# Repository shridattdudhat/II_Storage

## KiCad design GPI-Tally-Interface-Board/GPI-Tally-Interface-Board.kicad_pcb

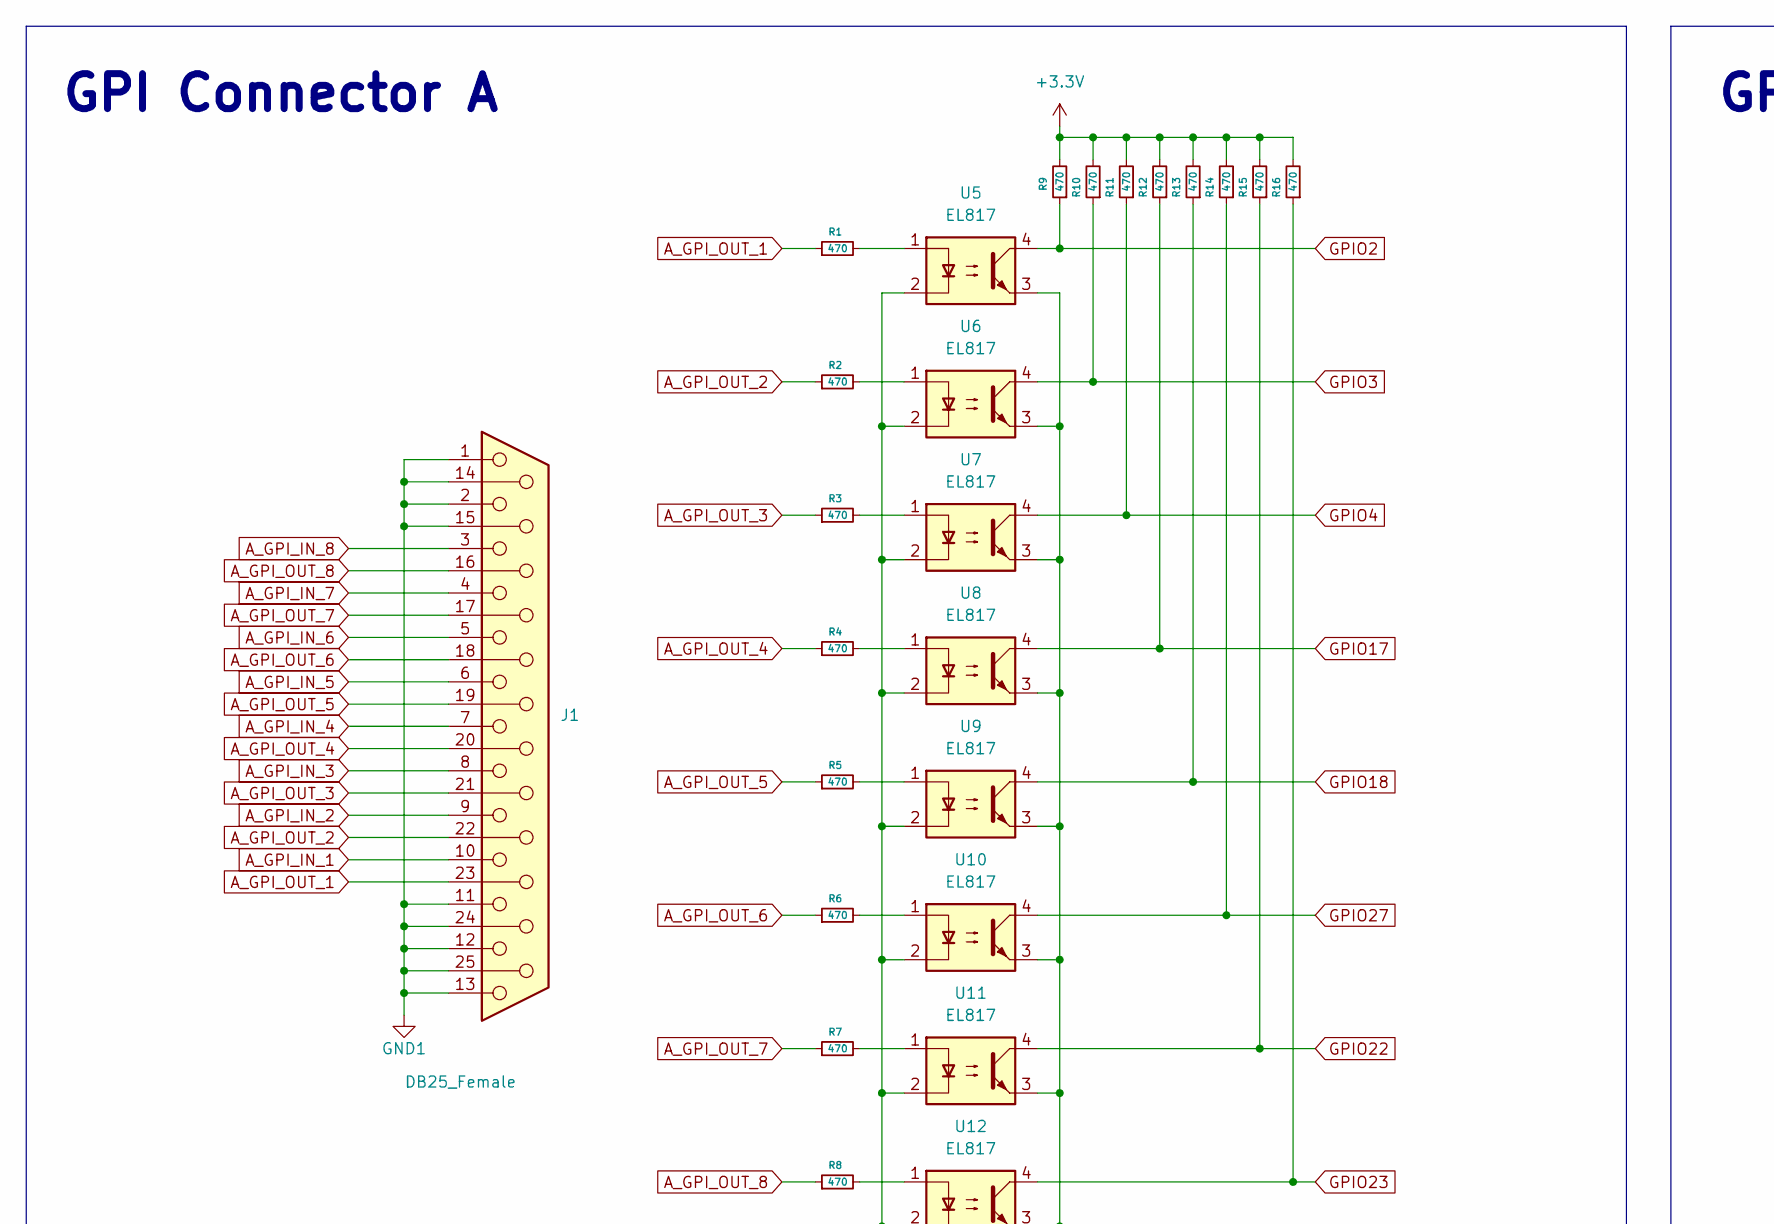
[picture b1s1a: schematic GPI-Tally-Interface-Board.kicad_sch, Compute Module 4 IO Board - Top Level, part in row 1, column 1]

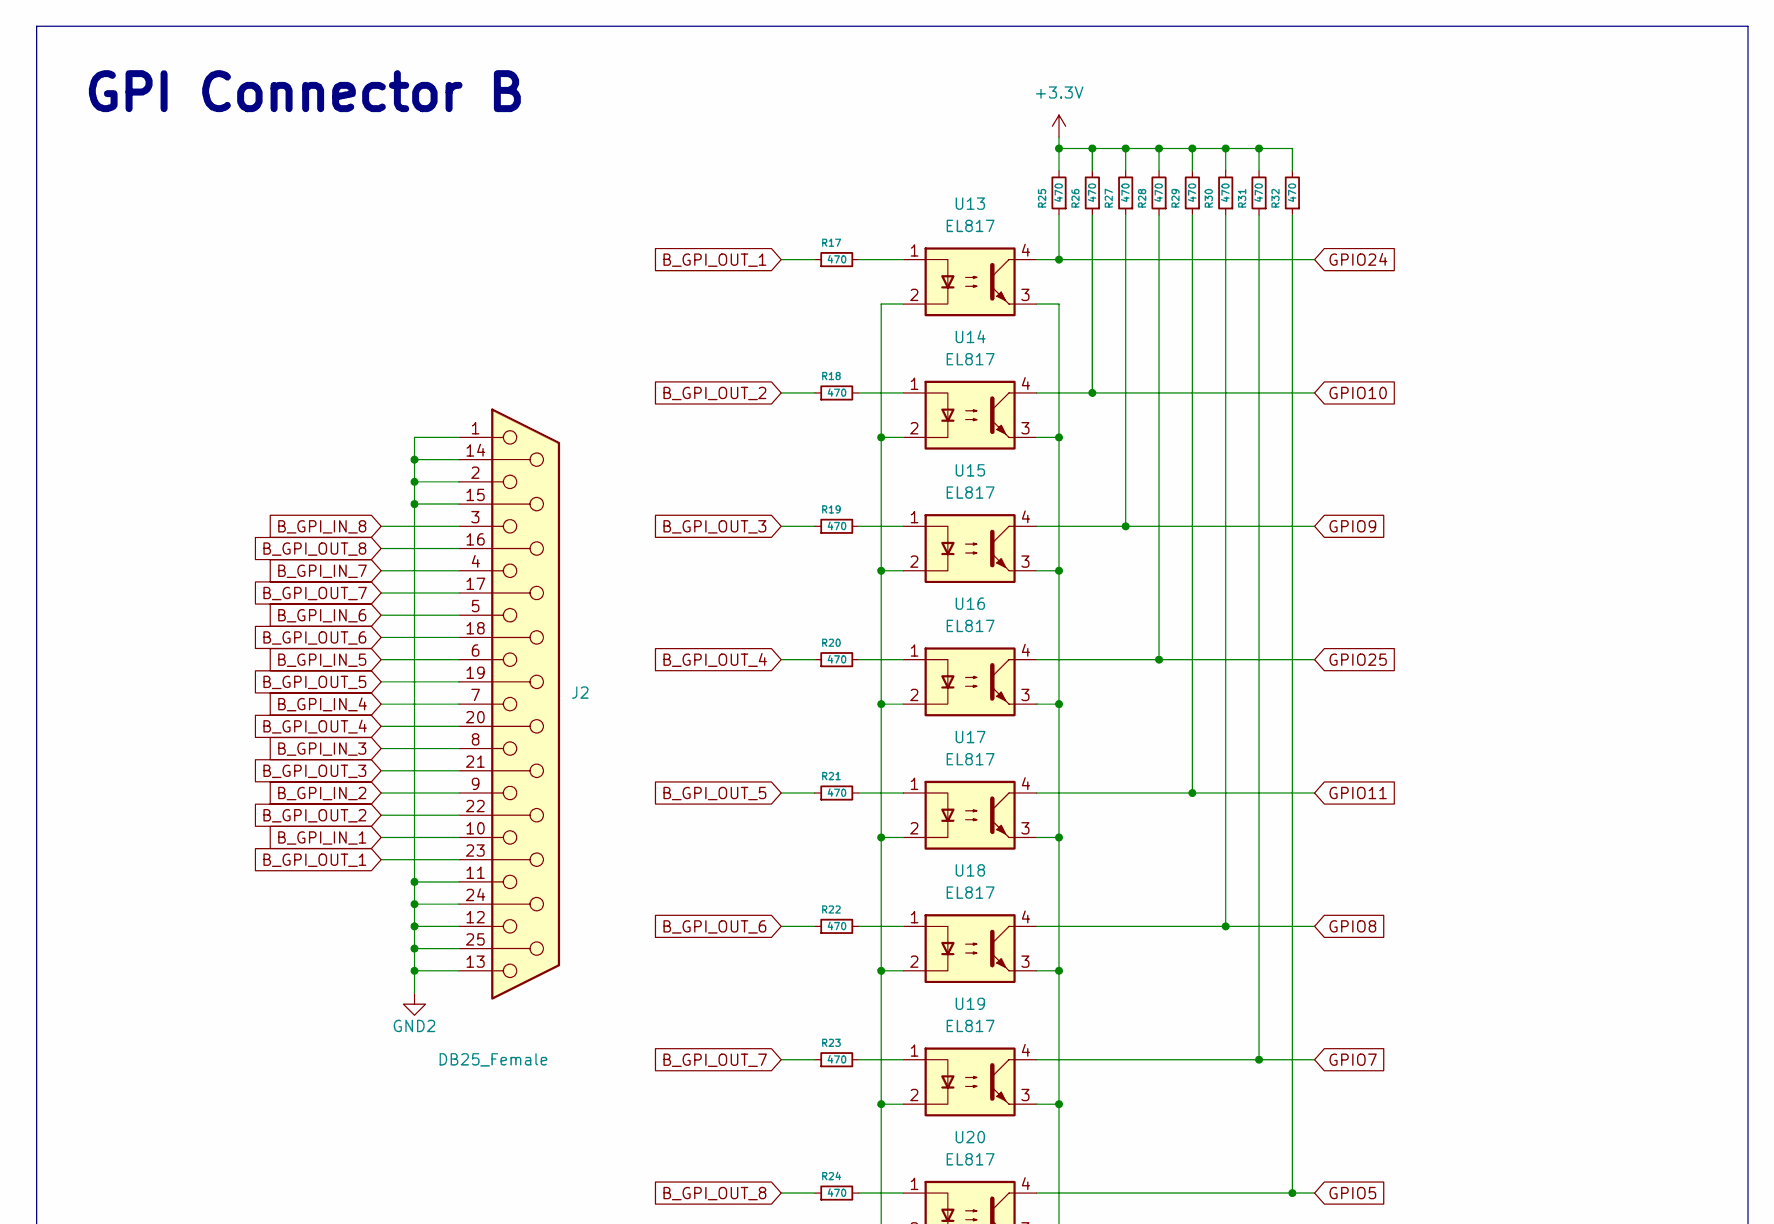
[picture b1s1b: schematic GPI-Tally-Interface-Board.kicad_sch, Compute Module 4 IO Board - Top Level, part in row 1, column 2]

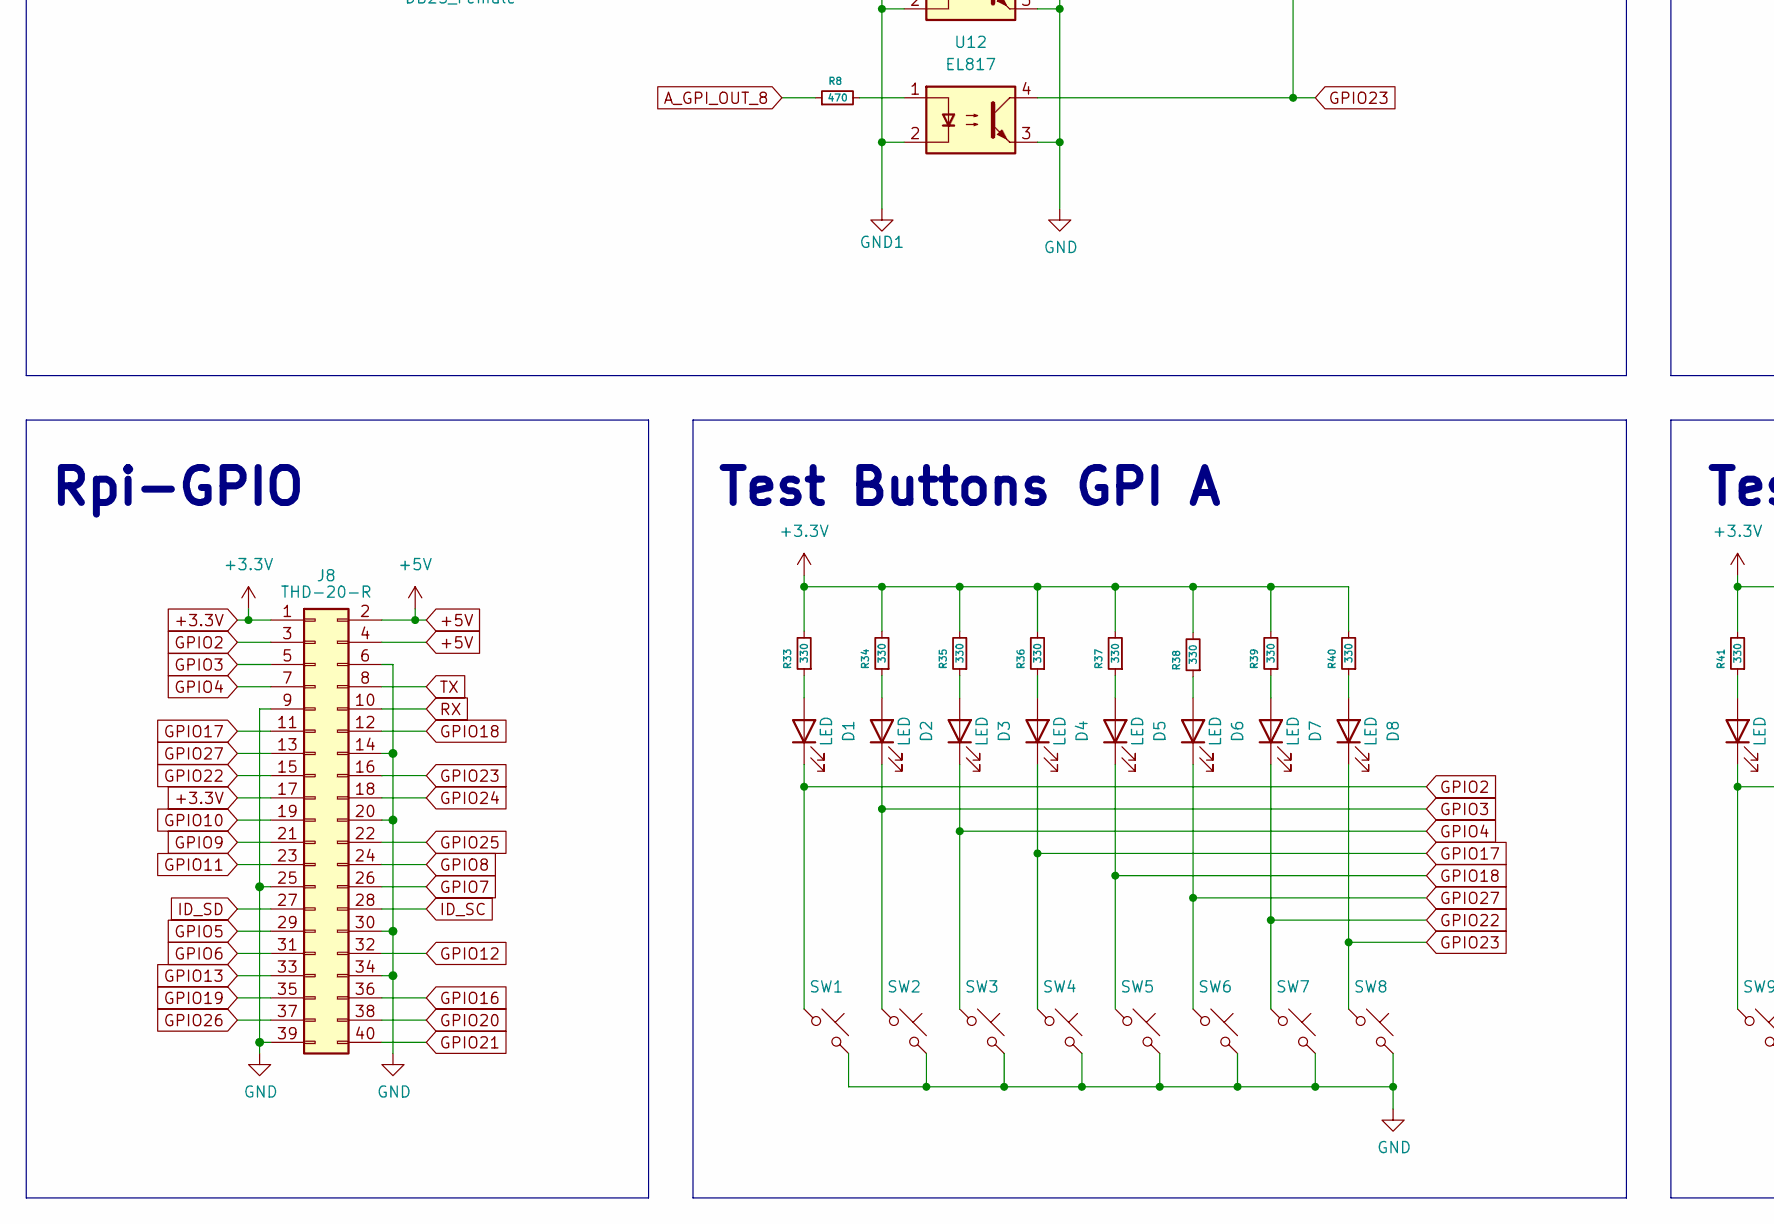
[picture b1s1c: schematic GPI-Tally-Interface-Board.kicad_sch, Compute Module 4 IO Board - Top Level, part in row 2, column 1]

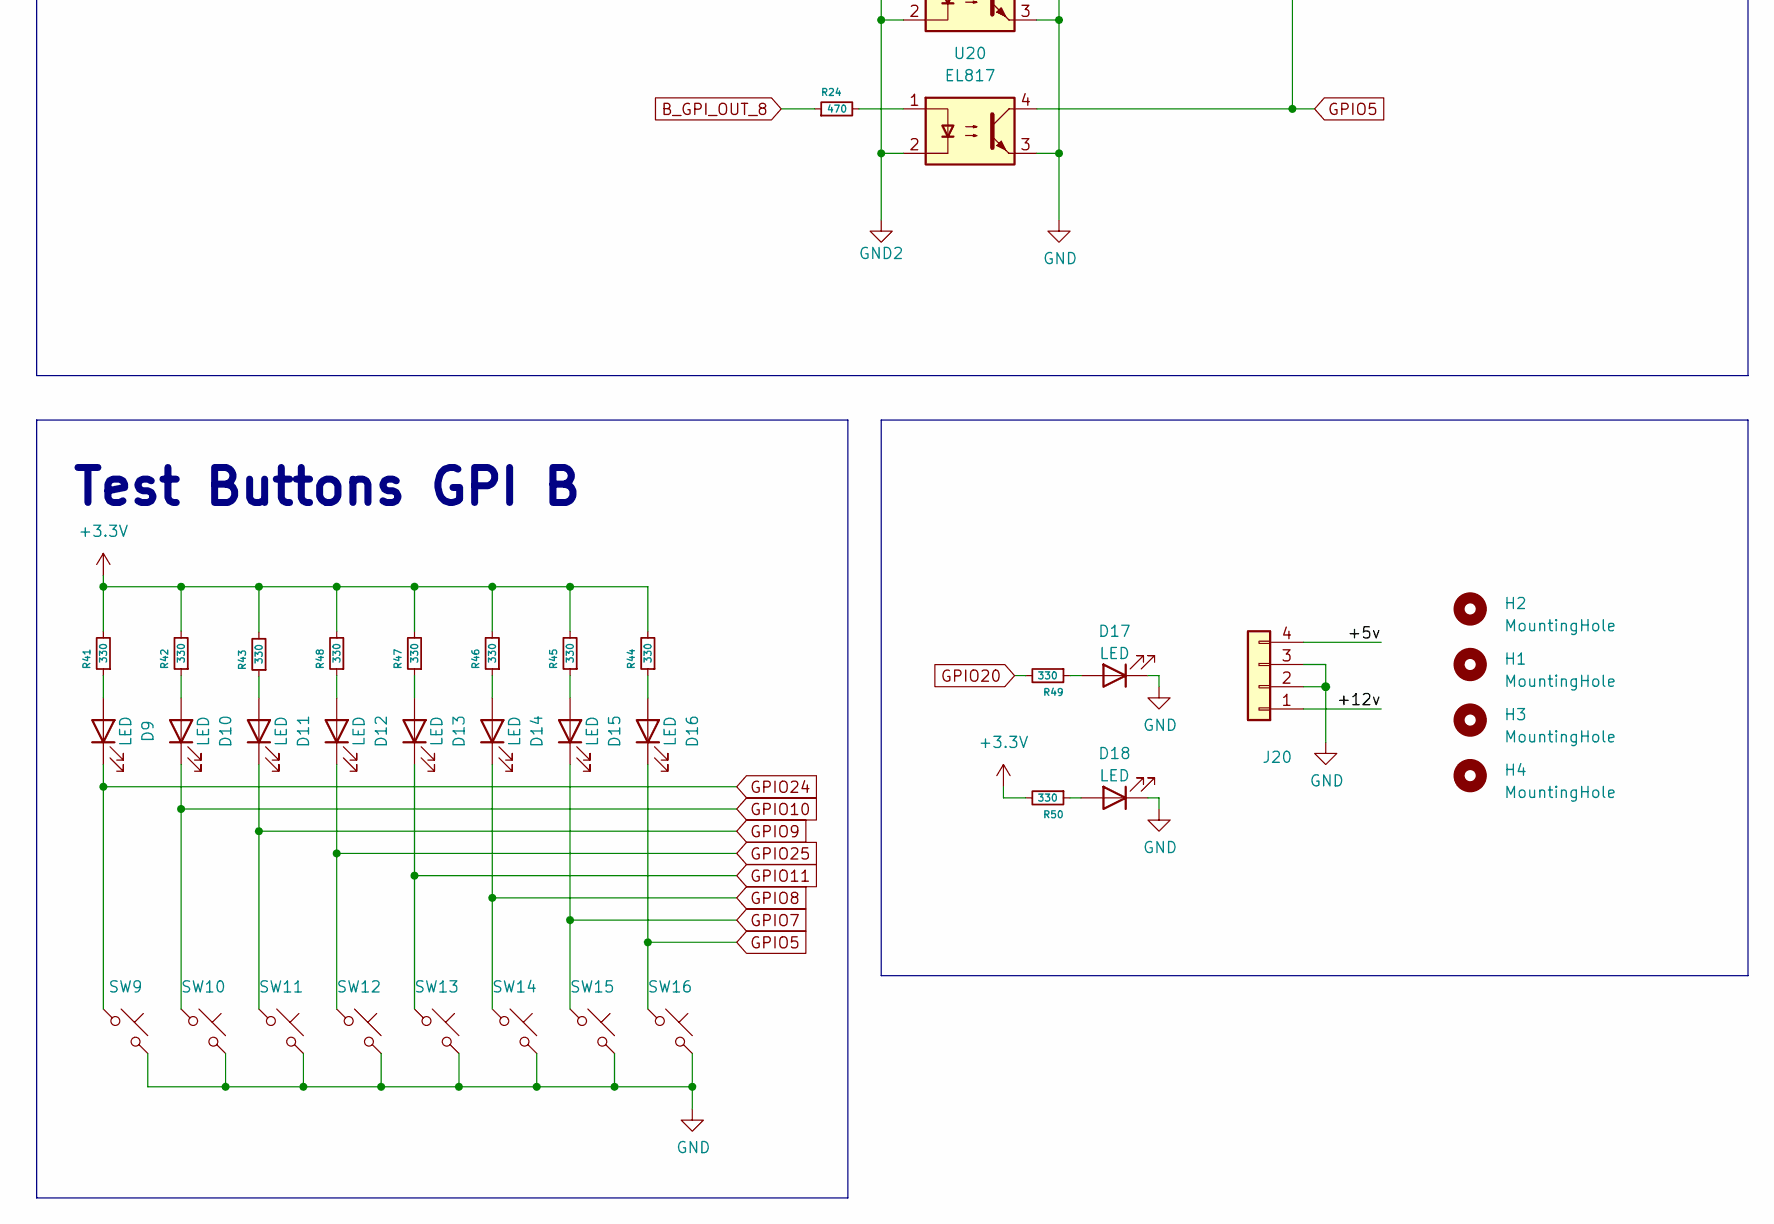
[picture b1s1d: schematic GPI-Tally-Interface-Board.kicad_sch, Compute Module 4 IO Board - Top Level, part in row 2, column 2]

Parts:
D1, D2, D3, D4, D5, D6, D7, D8, D9, D10, D11, D12, D13, D14, D15, D16: LED; LED_D5.0mm
D17: LED; LED_D5.0mm_IRGrey
D18: LED; LED_D5.0mm_Clear
H1, H2, H3, H4: MountingHole; MountingHole_3.2mm_M3
J1, J2: DB25_Female; DSUB-25_Female_Horizontal_P2.77x2.84mm_EdgePinOffset4.94mm_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
J8: THD-20-R; PinHeader_2x20_P2.54mm_Vertical; Part Description PinHeader_2x20_P2.54mm_Vertical
J20: AMP171826-4; TE_171826-4; Part Description Wire-To-Board Connector, Right Angle, 2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
R1, R2, R3, R4, R5, R6, R7, R8, R9, R10, R11, R12, R13, R14, R15, R16, R17, R18, R19, R20, R21, R22, R23, R24, R25, R26, R27, R28, R29, R30, R31, R32: 470; R_0805_2012Metric_Pad1.20x1.40mm_HandSolder
R33, R34, R35, R36, R37, R38, R39, R40, R41, R42, R43, R44, R45, R46, R47, R48, R49, R50: 330; R_0805_2012Metric_Pad1.20x1.40mm_HandSolder
SW1, SW2, SW3, SW4, SW5, SW6, SW7, SW8, SW9, SW10, SW11, SW12, SW13, SW14, SW15, SW16: SW_Push_45deg; SW_PUSH_6mm_H8mm
U5, U6, U7, U8, U9, U10, U11, U12, U13, U14, U15, U16, U17, U18, U19, U20: EL817; DIP-4_W7.62mm

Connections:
+3.3V: J8.1, J8.17, R9.2, R10.2, R11.2, R12.2, R13.2, R14.2, R15.2, R16.2, R25.2, R26.2, R27.2, R28.2, R29.2, R30.2, R31.2, R32.2, R33.2, R34.2, R35.2, R36.2, R37.2, R38.2, R39.2, R40.2, R41.2, R42.2, R43.2, R44.2, R45.2, R46.2, R47.2, R48.2, R50.2
+5V: J8.2, J8.4
/+5v: J20.4
/+12v: J20.1
A_GPI_IN_1: J1.10
A_GPI_IN_2: J1.9
A_GPI_IN_3: J1.8
A_GPI_IN_4: J1.7
A_GPI_IN_5: J1.6
A_GPI_IN_6: J1.5
A_GPI_IN_7: J1.4
A_GPI_IN_8: J1.3
A_GPI_OUT_1: J1.23, R1.1
A_GPI_OUT_2: J1.22, R2.1
A_GPI_OUT_3: J1.21, R3.1
A_GPI_OUT_4: J1.20, R4.1
A_GPI_OUT_5: J1.19, R5.1
A_GPI_OUT_6: J1.18, R6.1
A_GPI_OUT_7: J1.17, R7.1
A_GPI_OUT_8: J1.16, R8.1
B_GPI_IN_1: J2.10
B_GPI_IN_2: J2.9
B_GPI_IN_3: J2.8
B_GPI_IN_4: J2.7
B_GPI_IN_5: J2.6
B_GPI_IN_6: J2.5
B_GPI_IN_7: J2.4
B_GPI_IN_8: J2.3
B_GPI_OUT_1: J2.23, R17.1
B_GPI_OUT_2: J2.22, R18.1
B_GPI_OUT_3: J2.21, R19.1
B_GPI_OUT_4: J2.20, R20.1
B_GPI_OUT_5: J2.19, R21.1
B_GPI_OUT_6: J2.18, R22.1
B_GPI_OUT_7: J2.17, R23.1
B_GPI_OUT_8: J2.16, R24.1
GND: D17.1 (K), D18.1 (K), J8.6, J8.9, J8.14, J8.20, J8.25, J8.30, J8.34, J8.39, J20.2, J20.3, SW1.2, SW2.2, SW3.2, SW4.2, SW5.2, SW6.2, SW7.2, SW8.2, SW9.2, SW10.2, SW11.2, SW12.2, SW13.2, SW14.2, SW15.2, SW16.2, U5.3, U6.3, U7.3, U8.3, U9.3, U10.3, U11.3, U12.3, U13.3, U14.3, U15.3, U16.3, U17.3, U18.3, U19.3, U20.3
GND1: J1.1, J1.2, J1.11, J1.12, J1.13, J1.14, J1.15, J1.24, J1.25, U5.2, U6.2, U7.2, U8.2, U9.2, U10.2, U11.2, U12.2
GND2: J2.1, J2.2, J2.11, J2.12, J2.13, J2.14, J2.15, J2.24, J2.25, U13.2, U14.2, U15.2, U16.2, U17.2, U18.2, U19.2, U20.2
GPIO2: D1.1 (K), J8.3, R9.1, SW1.1, U5.4
GPIO3: D2.1 (K), J8.5, R10.1, SW2.1, U6.4
GPIO4: D3.1 (K), J8.7, R11.1, SW3.1, U7.4
GPIO5: D16.1 (K), J8.29, R32.1, SW16.1, U20.4
GPIO6: J8.31
GPIO7: D15.1 (K), J8.26, R31.1, SW15.1, U19.4
GPIO8: D14.1 (K), J8.24, R30.1, SW14.1, U18.4
GPIO9: D11.1 (K), J8.21, R27.1, SW11.1, U15.4
GPIO10: D10.1 (K), J8.19, R26.1, SW10.1, U14.4
GPIO11: D13.1 (K), J8.23, R29.1, SW13.1, U17.4
GPIO12: J8.32
GPIO13: J8.33
GPIO16: J8.36
GPIO17: D4.1 (K), J8.11, R12.1, SW4.1, U8.4
GPIO18: D5.1 (K), J8.12, R13.1, SW5.1, U9.4
GPIO19: J8.35
GPIO20: J8.38, R49.2
GPIO21: J8.40
GPIO22: D7.1 (K), J8.15, R15.1, SW7.1, U11.4
GPIO23: D8.1 (K), J8.16, R16.1, SW8.1, U12.4
GPIO24: D9.1 (K), J8.18, R25.1, SW9.1, U13.4
GPIO25: D12.1 (K), J8.22, R28.1, SW12.1, U16.4
GPIO26: J8.37
GPIO27: D6.1 (K), J8.13, R14.1, SW6.1, U10.4
ID_SC: J8.28
ID_SD: J8.27
unnamed: D1.2 (A), R33.1
unnamed: D2.2 (A), R34.1
unnamed: D3.2 (A), R35.1
unnamed: D4.2 (A), R36.1
unnamed: D5.2 (A), R37.1
unnamed: D6.2 (A), R38.1
unnamed: D7.2 (A), R39.1
unnamed: D8.2 (A), R40.1
unnamed: D9.2 (A), R41.1
unnamed: D10.2 (A), R42.1
unnamed: D11.2 (A), R43.1
unnamed: D17.2 (A), R49.1
unnamed: D18.2 (A), R50.1
unnamed: R1.2, U5.1
unnamed: R2.2, U6.1
unnamed: R3.2, U7.1
unnamed: R4.2, U8.1
unnamed: R5.2, U9.1
unnamed: R6.2, U10.1
unnamed: R7.2, U11.1
unnamed: R8.2, U12.1
unnamed: R17.2, U13.1
unnamed: R18.2, U14.1
unnamed: R19.2, U15.1
unnamed: R20.2, U16.1
unnamed: R21.2, U17.1
unnamed: R22.2, U18.1
unnamed: R23.2, U19.1
unnamed: R24.2, U20.1
unnamed: D16.2 (A), R44.1
unnamed: D15.2 (A), R45.1
unnamed: D14.2 (A), R46.1
unnamed: D13.2 (A), R47.1
unnamed: D12.2 (A), R48.1
RX: J8.10
TX: J8.8

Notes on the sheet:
Test Buttons GPI B
GPI Connector A
GPI Connector B
Rpi-GPIO
Test Buttons GPI A

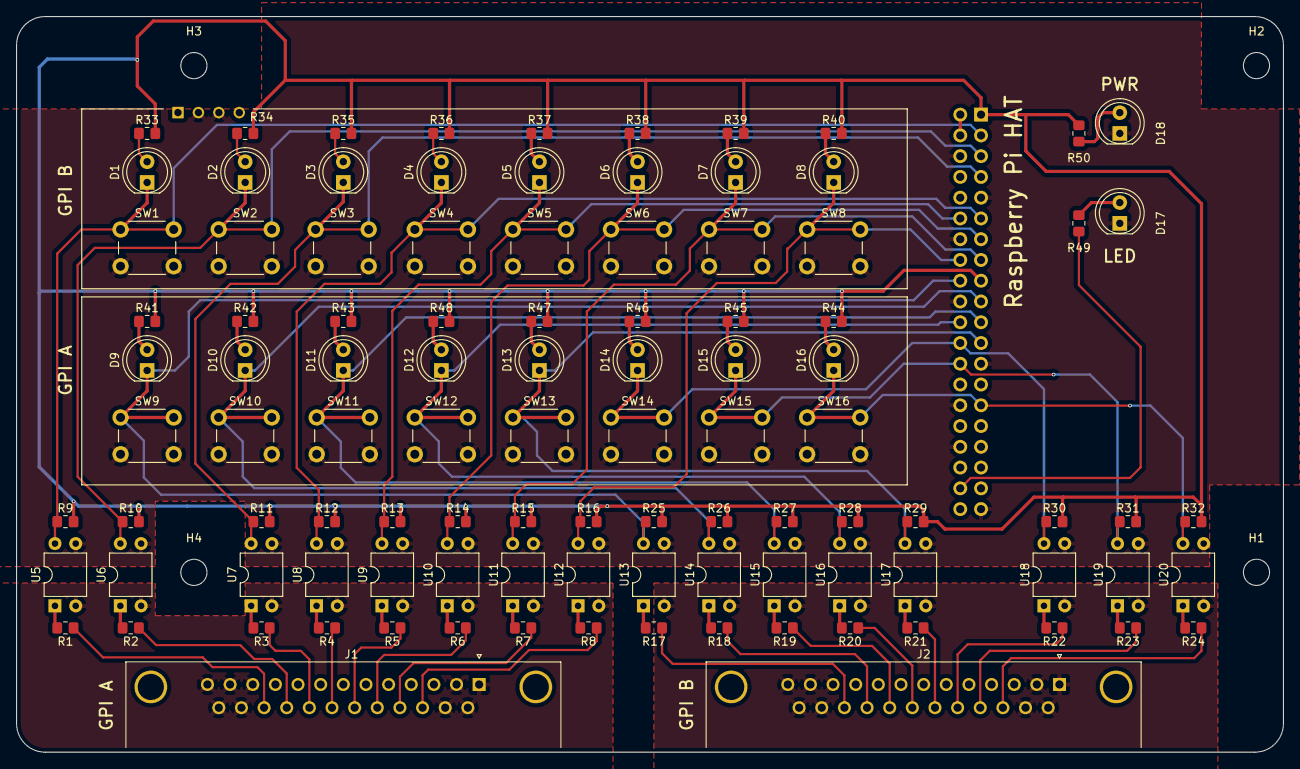
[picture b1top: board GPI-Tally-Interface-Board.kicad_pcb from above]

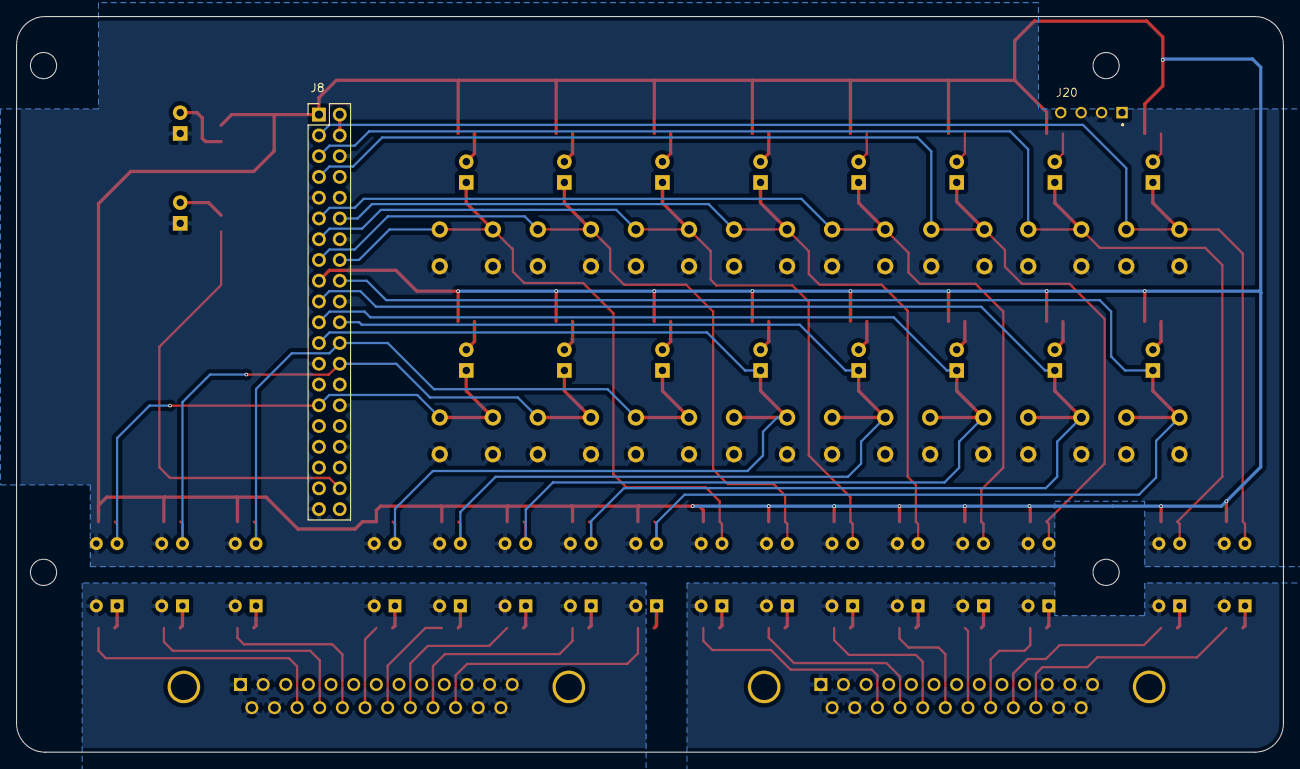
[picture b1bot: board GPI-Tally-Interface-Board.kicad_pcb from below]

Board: 2 copper layers, 155.0 x 90.0 mm, 108 parts (2 on the bottom side), 72 nets.

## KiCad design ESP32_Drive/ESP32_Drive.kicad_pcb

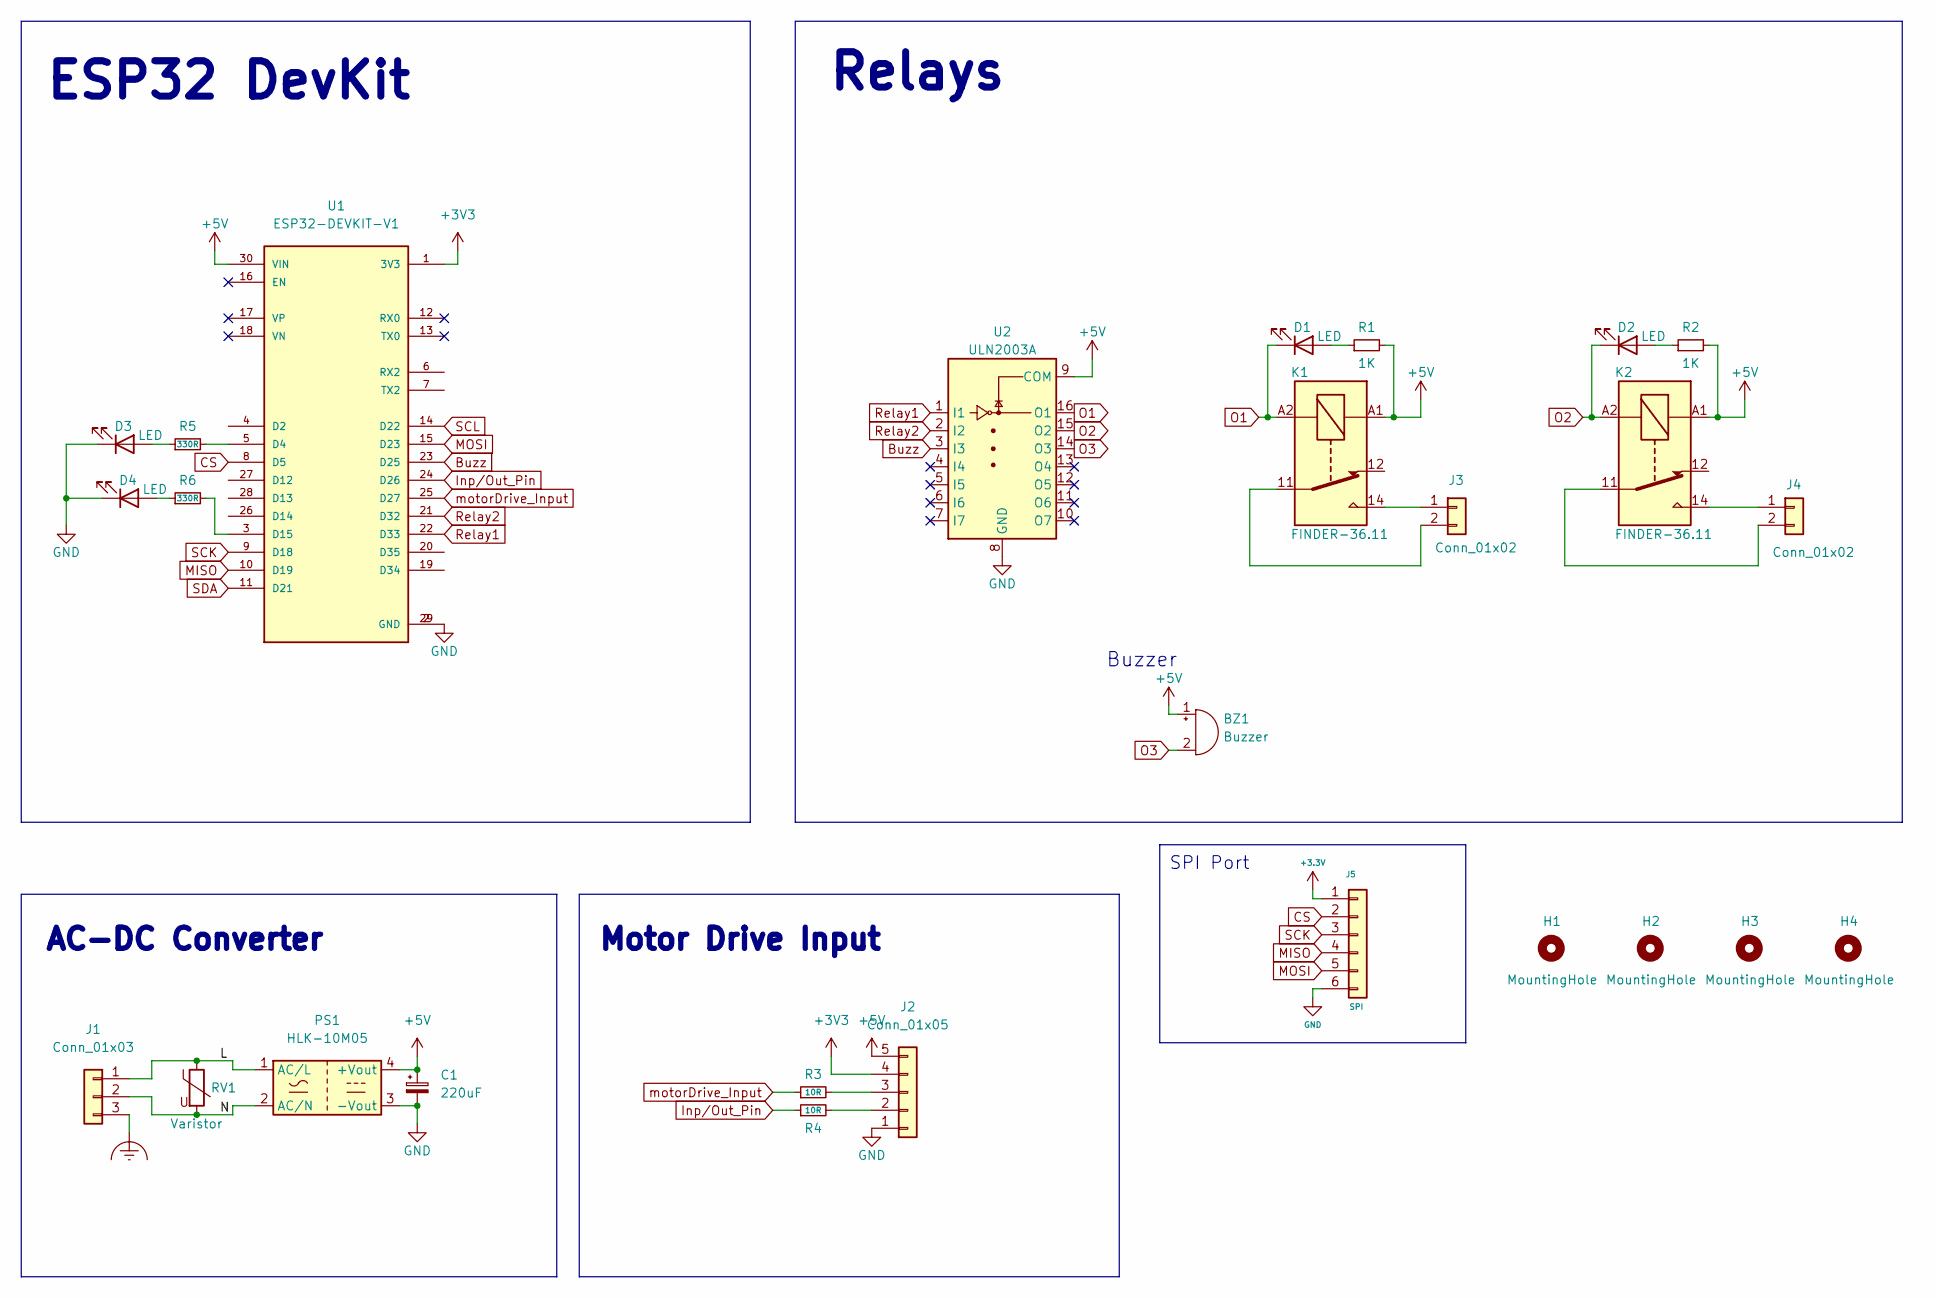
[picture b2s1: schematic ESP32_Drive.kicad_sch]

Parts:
BZ1: Buzzer; Buzzer_12x9.5RM7.6
C1: 220uF; CP_Radial_D8.0mm_P3.50mm
D1, D2, D3, D4: LED; LED_1206_3216Metric_Pad1.42x1.75mm_HandSolder
H1, H2, H3, H4: MountingHole; MountingHole_3.5mm
J1: Conn_01x03; TerminalBlock_bornier-3_P5.08mm
J2: Conn_01x05; TerminalBlock_bornier-5_P5.08mm
J3, J4: Conn_01x02; TerminalBlock_bornier-2_P5.08mm
J5: SPI; PinHeader_1x06_P2.54mm_Vertical
K1, K2: FINDER-36.11; Relay_SPDT_Finder_36.11
PS1: HLK-10M05; HLK10M05
R1, R2: 1K; R_0805_2012Metric_Pad1.20x1.40mm_HandSolder
R3, R4: 10R; R_0805_2012Metric_Pad1.20x1.40mm_HandSolder
R5, R6: 330R; R_0805_2012Metric_Pad1.20x1.40mm_HandSolder
RV1: Varistor; RV_Disc_D12mm_W3.9mm_P7.5mm
U1: ESP32-DEVKIT-V1; MODULE_ESP32_DEVKIT_V1; PARTREV N/A
U2: ULN2003A; SOIC-16_3.9x9.9mm_P1.27mm

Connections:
+5V: BZ1.1 (-), C1.1, J2.5, K1.A1, K2.A1, PS1.4 (+Vout), R1.2, R2.2, U1.30 (VIN), U2.9 (COM)
/L: J1.1, PS1.1 (AC/L), RV1.1
/N: J1.2, PS1.2 (AC/N), RV1.2
Buzz: U1.23 (D25), U2.3 (I3)
CS: J5.2, U1.8 (D5)
Earth_Clean: J1.3
GND: C1.2, D3.1 (K), D4.1 (K), J2.1, J5.6, PS1.3 (-Vout), U1.2 (GND), U1.29 (GND), U2.8 (GND)
Inp/Out_Pin: R4.1, U1.24 (D26)
MISO: J5.4, U1.10 (D19)
MOSI: J5.5, U1.15 (D23)
unnamed: D1.2 (A), R1.1
unnamed: D2.2 (A), R2.1
unnamed: J2.2, R4.2
unnamed: J2.3, R3.2
unnamed: J3.1, K1.14
unnamed: J3.2, K1.11
unnamed: J4.1, K2.14
unnamed: J4.2, K2.11
unnamed: D3.2 (A), R5.1
unnamed: D4.2 (A), R6.1
unnamed: R6.2, U1.3 (D15)
unnamed: R5.2, U1.5 (D4)
O1: D1.1 (K), K1.A2, U2.16 (O1)
O2: D2.1 (K), K2.A2, U2.15 (O2)
O3: BZ1.2 (+), U2.14 (O3)
Relay1: U1.22 (D33), U2.1 (I1)
Relay2: U1.21 (D32), U2.2 (I2)
SCK: J5.3, U1.9 (D18)
SCL: U1.14 (D22)
SDA: U1.11 (D21)
motorDrive_Input: R3.1, U1.25 (D27)

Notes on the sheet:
Motor Drive Input
Relays
Buzzer
ESP32 DevKit
SPI Port
AC-DC Converter

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
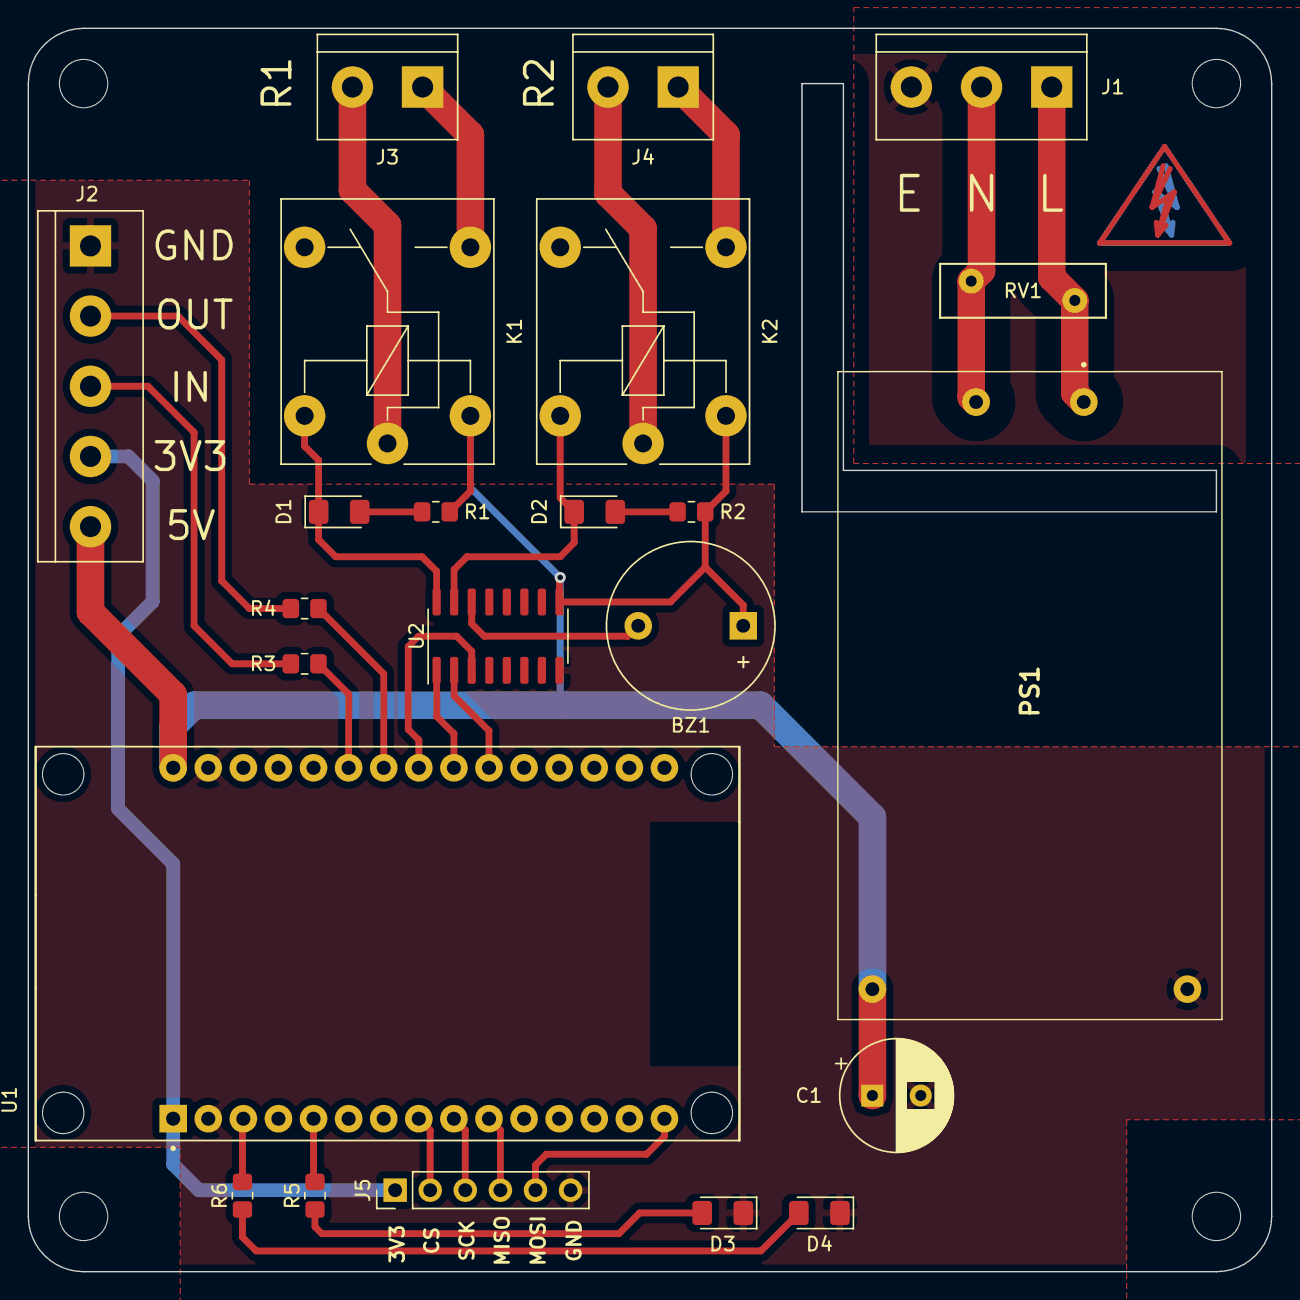
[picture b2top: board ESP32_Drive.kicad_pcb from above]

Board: 2 copper layers, 90.0 x 90.0 mm, 27 parts (0 on the bottom side), 29 nets.

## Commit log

2022-11-20 GPI Tally
2022-11-24 oppto added
2022-11-24 esp32 drive
2022-11-24 mirror
2022-11-29 gerber
2022-12-31 clean
